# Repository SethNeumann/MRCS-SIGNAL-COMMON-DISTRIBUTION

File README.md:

# REPO NAME:     MRCS-SIGNAL-COMMON-DISTRIBUTION

## License: Creative Commons Attribution-NonCommercial-ShareAlike

 MRCS-SIGNAL-COMMON-DISTRIBUTION

 As "We Honest" signals become more popular, many users prefer to use a single limiting resistor per head, rather than a resistor per signal line (R/Y/G). This board provides 3 8-segment SIPs to 
 power up to 24 common leads (usually anode, but no reason it won't work for cathodes). The board features a barrel jack and a 4 position screw terminal for power input (ground is just passed through).
 Two 12 position 0.100 screw terminals provide connections to the signal heads.

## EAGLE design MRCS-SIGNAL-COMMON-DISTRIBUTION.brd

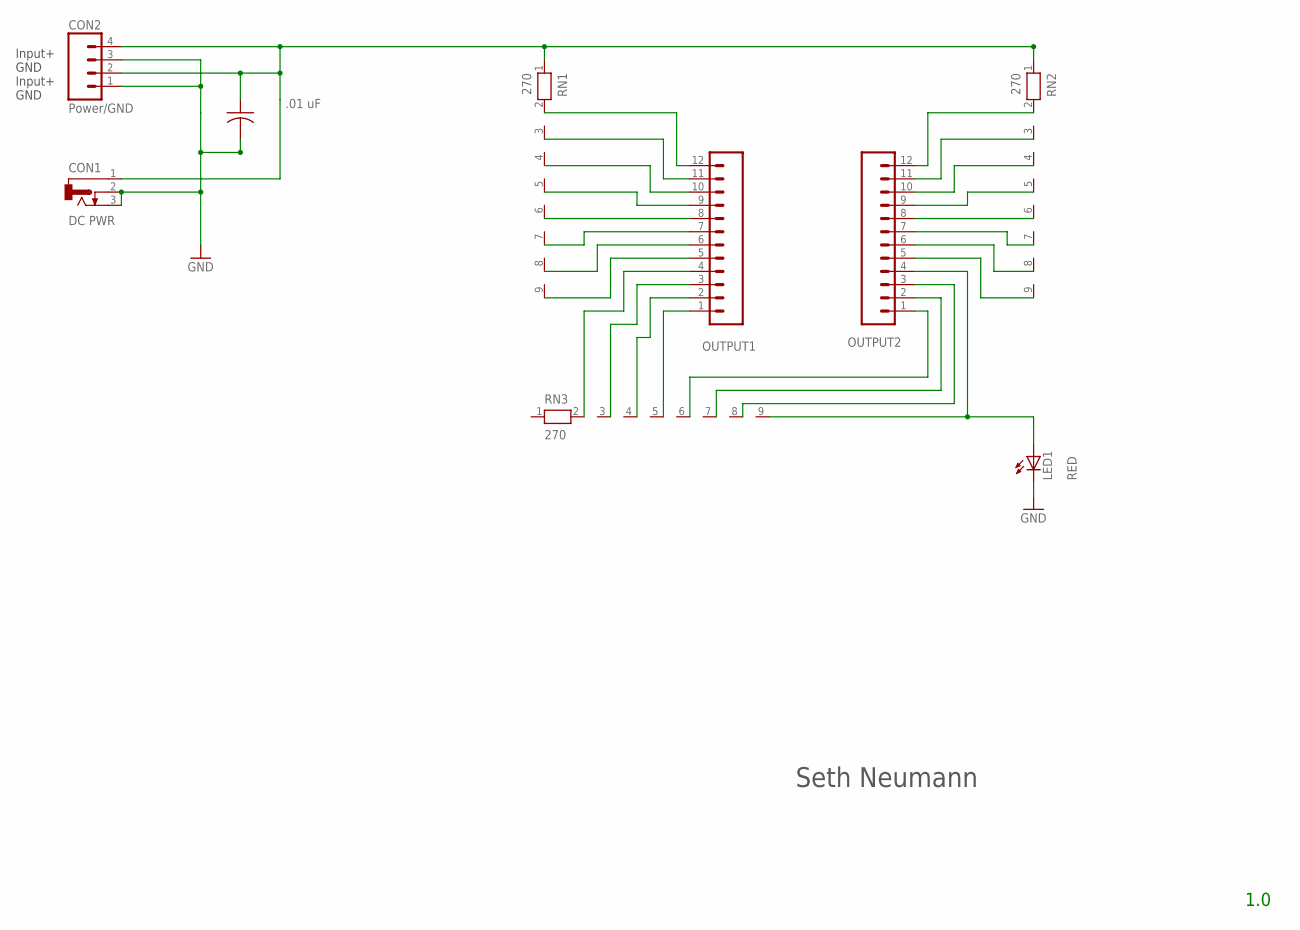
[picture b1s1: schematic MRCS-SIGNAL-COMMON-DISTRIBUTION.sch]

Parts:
C1: .01 uF; C050-024X044
CON1: DC PWR; DCJ0202
CON2: Power/GND; SCREWTERMINAL-3.5MM-4_LOCK
CON3: OUTPUT1; 1X12_LOCK
CON4: OUTPUT2; 1X12_LOCK
LED1: RED; LED3MM
RN1, RN2, RN3: 270; RN-9

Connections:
GND: C1.2, CON1.2, CON1.3, CON2.1, CON2.3, LED1.K (C)
INPUT+: C1.1, CON1.1, CON2.2, CON2.4, RN1.1, RN2.1
unnamed: CON3.12, RN1.2
unnamed: CON3.11, RN1.3
unnamed: CON3.10, RN1.4
unnamed: CON3.9, RN1.5
unnamed: CON3.8, RN1.6
unnamed: CON3.7, RN1.7
unnamed: CON3.6, RN1.8
unnamed: CON3.5, RN1.9
unnamed: CON4.12, RN2.2
unnamed: CON4.11, RN2.3
unnamed: CON4.10, RN2.4
unnamed: CON4.9, RN2.5
unnamed: CON4.8, RN2.6
unnamed: CON4.7, RN2.7
unnamed: CON4.6, RN2.8
unnamed: CON4.5, RN2.9
unnamed: CON3.4, RN3.2
unnamed: CON3.3, RN3.3
unnamed: CON3.2, RN3.4
unnamed: CON3.1, RN3.5
unnamed: CON4.1, RN3.6
unnamed: CON4.4, LED1.A, RN3.9
unnamed: CON4.3, RN3.8
unnamed: CON4.2, RN3.7

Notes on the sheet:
Input+ GND Input+ GND
Seth Neumann
1.0

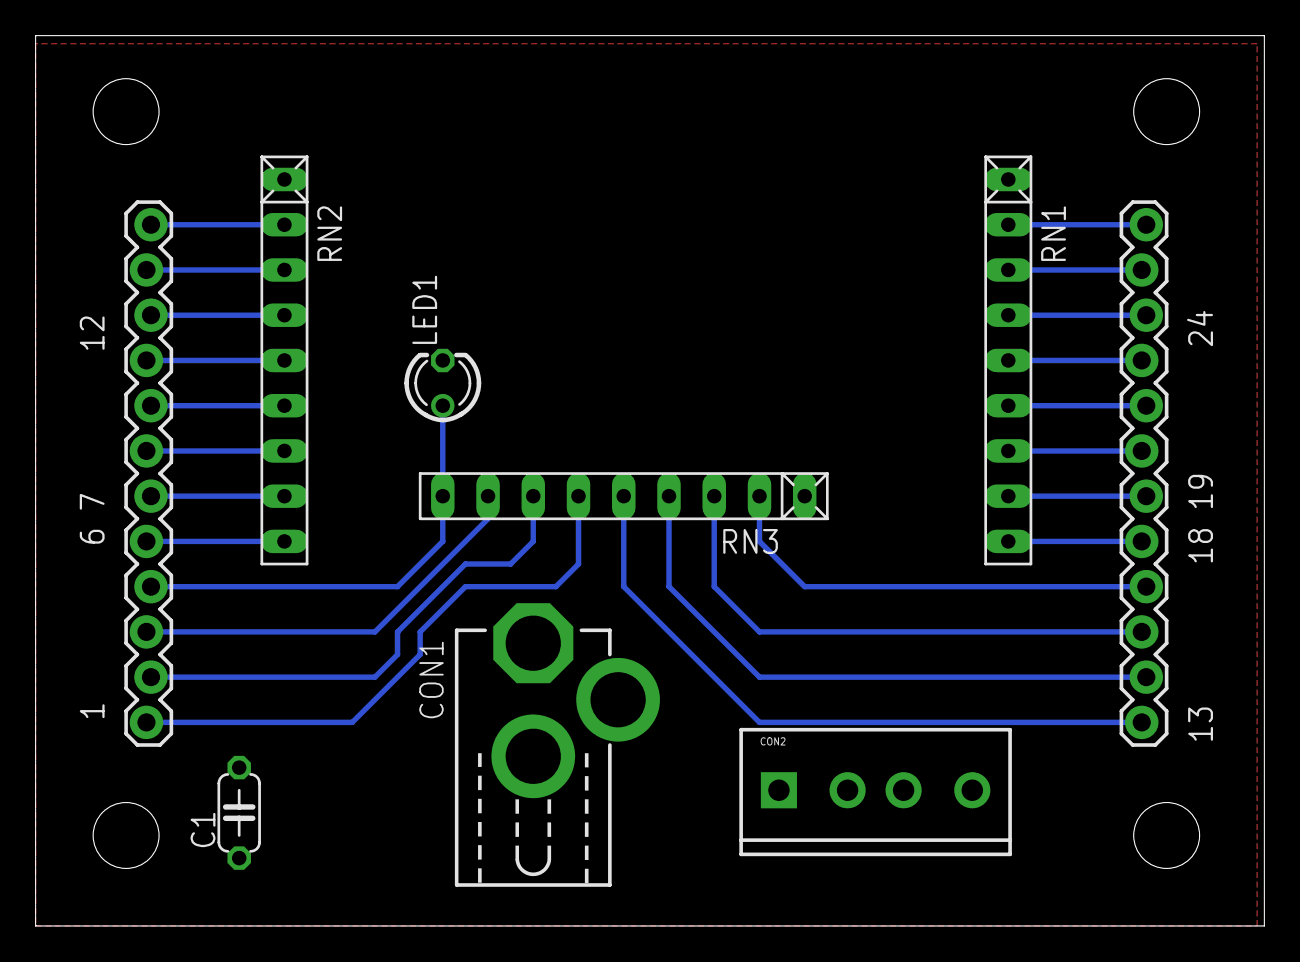
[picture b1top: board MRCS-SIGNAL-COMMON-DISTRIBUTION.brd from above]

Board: 2 copper layers, 69.0 x 50.0 mm, 12 parts (0 on the bottom side), 26 nets.

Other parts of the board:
U$1: CA-PROP65WARNING
U$2: MRCSLOGOTOP
U$3: MRCSLOGOBTM

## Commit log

2024-01-26 organizing files to start project
2024-01-27 initial board for testing
    first pass, this is based on the Buckeroo footprint
2024-01-27 last minute fixes
    added Prop 65 label and bottom logo
